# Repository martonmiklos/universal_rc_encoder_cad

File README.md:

# Universal R/C encoder

This repo hosts the CAD files of the Universal R/C encoder circuit drawn in EAGLE. 

Firmware can be found [here](https://github.com/martonmiklos/universal_rc_encoder_fw)

The goal of this project to provide an "addon" PCB which is capable of emulating various R/C toy encoder ICs.
 * TX2/RX2
 * Nikko C1069C
 * TAIYO ??
 * Standard PPM for backward compatiblity

The PCB is based on the 3rd USD STM8S003F3 and it is shaped to be able to installed in the place of an NE5044 encoder.

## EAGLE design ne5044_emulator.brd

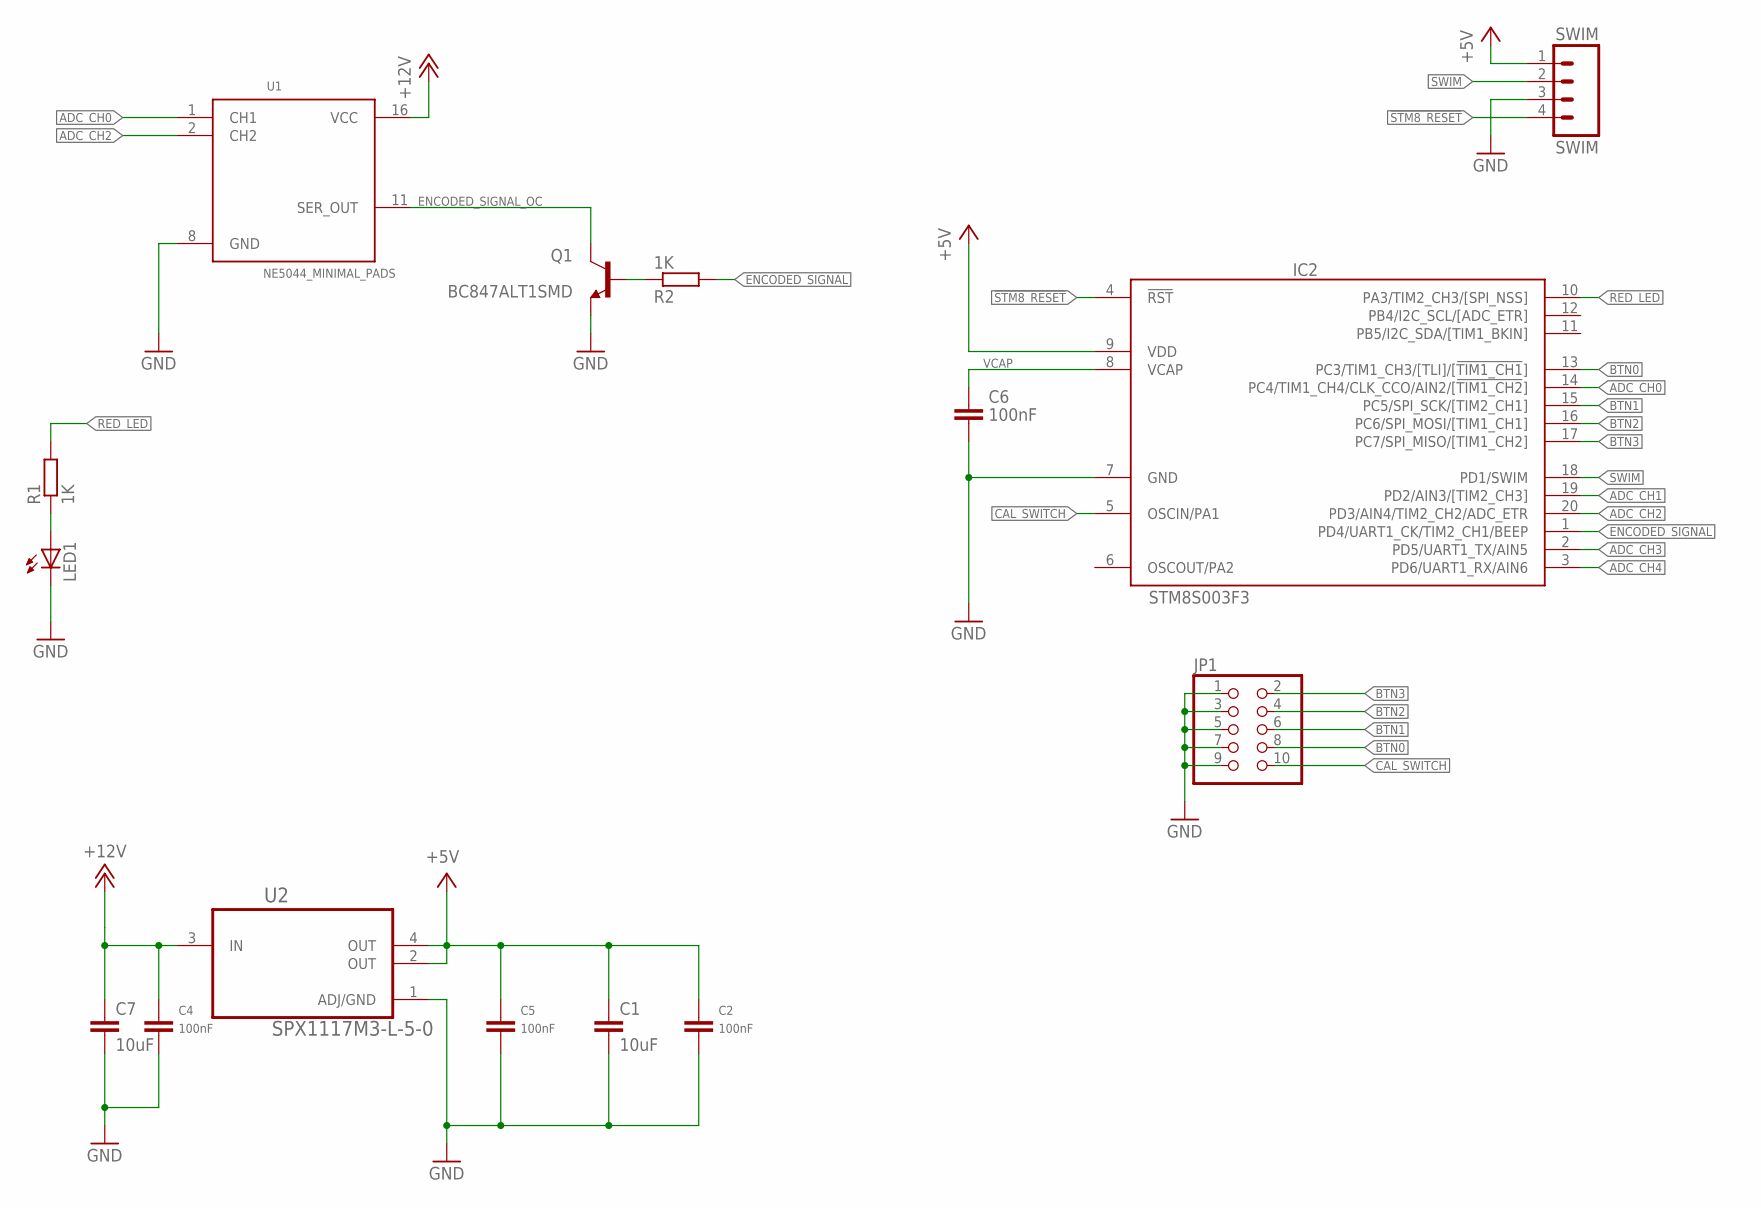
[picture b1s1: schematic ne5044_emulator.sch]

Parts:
C1, C7: 10uF; C0805
C2, C4, C5: 100nF; C0603K
C6: 100nF; C0603
IC2: STM8S003F3; TSSOP20
JP1: PINHD-2X5; 2X05
LED1: LEDCHIP-LED0603; CHIP-LED0603
Q1: BC847ALT1SMD; SOT23
R1, R2: 1K; R0603
SWIM: SWIM; 1X04-1.27MM
U1: NE5044_MINIMAL_PADS; DIL16_MINIMAL_PADS_FOR_NE5044
U2: SPX1117M3-L-5-0; SOT230P696X180-4N

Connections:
!STM8_RESET: IC2.4 (!RST), SWIM.4
+5V: C1.1, C2.1, C5.1, IC2.9 (VDD), SWIM.1, U2.2 (OUT), U2.4 (OUT)
+12V: C4.1, C7.1, U1.16 (VCC), U2.3 (IN)
ADC_CH0: IC2.14 (PC4/TIM1_CH4/CLK_CCO/AIN2/[!TIM1_CH2!]), U1.1 (CH1)
ADC_CH1: IC2.19 (PD2/AIN3/[TIM2_CH3])
ADC_CH2: IC2.20 (PD3/AIN4/TIM2_CH2/ADC_ETR), U1.2 (CH2)
ADC_CH3: IC2.2 (PD5/UART1_TX/AIN5)
ADC_CH4: IC2.3 (PD6/UART1_RX/AIN6)
BTN0: IC2.13 (PC3/TIM1_CH3/[TLI]/[!TIM1_CH1!]), JP1.8
BTN1: IC2.15 (PC5/SPI_SCK/[TIM2_CH1]), JP1.6
BTN2: IC2.16 (PC6/SPI_MOSI/[TIM1_CH1]), JP1.4
BTN3: IC2.17 (PC7/SPI_MISO/[TIM1_CH2]), JP1.2
CAL_SWITCH: IC2.5 (OSCIN/PA1), JP1.10
ENCODED_SIGNAL: IC2.1 (PD4/UART1_CK/TIM2_CH1/BEEP), R2.2
ENCODED_SIGNAL_OC: Q1.3 (C), U1.11 (SER_OUT)
GND: C1.2, C2.2, C4.2, C5.2, C6.2, C7.2, IC2.7 (GND), JP1.1, JP1.3, JP1.5, JP1.7, JP1.9, LED1.C, Q1.2 (E), SWIM.3, U1.8 (GND), U2.1 (ADJ/GND)
unnamed: LED1.A, R1.1
unnamed: Q1.1 (B), R2.1
RED_LED: IC2.10 (PA3/TIM2_CH3/[SPI_NSS]), R1.2
SWIM: IC2.18 (PD1/SWIM), SWIM.2
VCAP: C6.1, IC2.8 (VCAP)

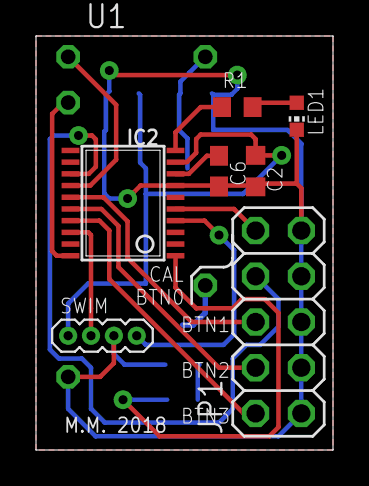
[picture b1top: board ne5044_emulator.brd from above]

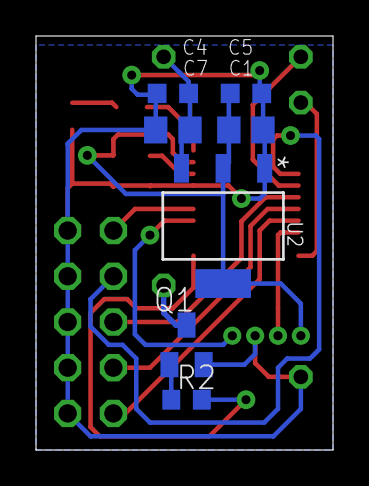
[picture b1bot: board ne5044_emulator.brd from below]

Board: 2 copper layers, 16.5 x 23.0 mm, 15 parts (7 on the bottom side), 18 nets.

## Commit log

2018-07-18 Add design files
2018-10-11 - Daily save
2018-10-11 - Release dirty production data
2018-10-11 - Add output transistor

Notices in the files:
parts and their libraries:
SparkFun: Licensing: CC v3.0 Share-Alike You are welcome to use this library for commercial purposes.
